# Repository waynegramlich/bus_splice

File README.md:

bus_splice
==========

Splice two buses together.

## Rev A. Issues

* Are terminal blocks oriented backwards?

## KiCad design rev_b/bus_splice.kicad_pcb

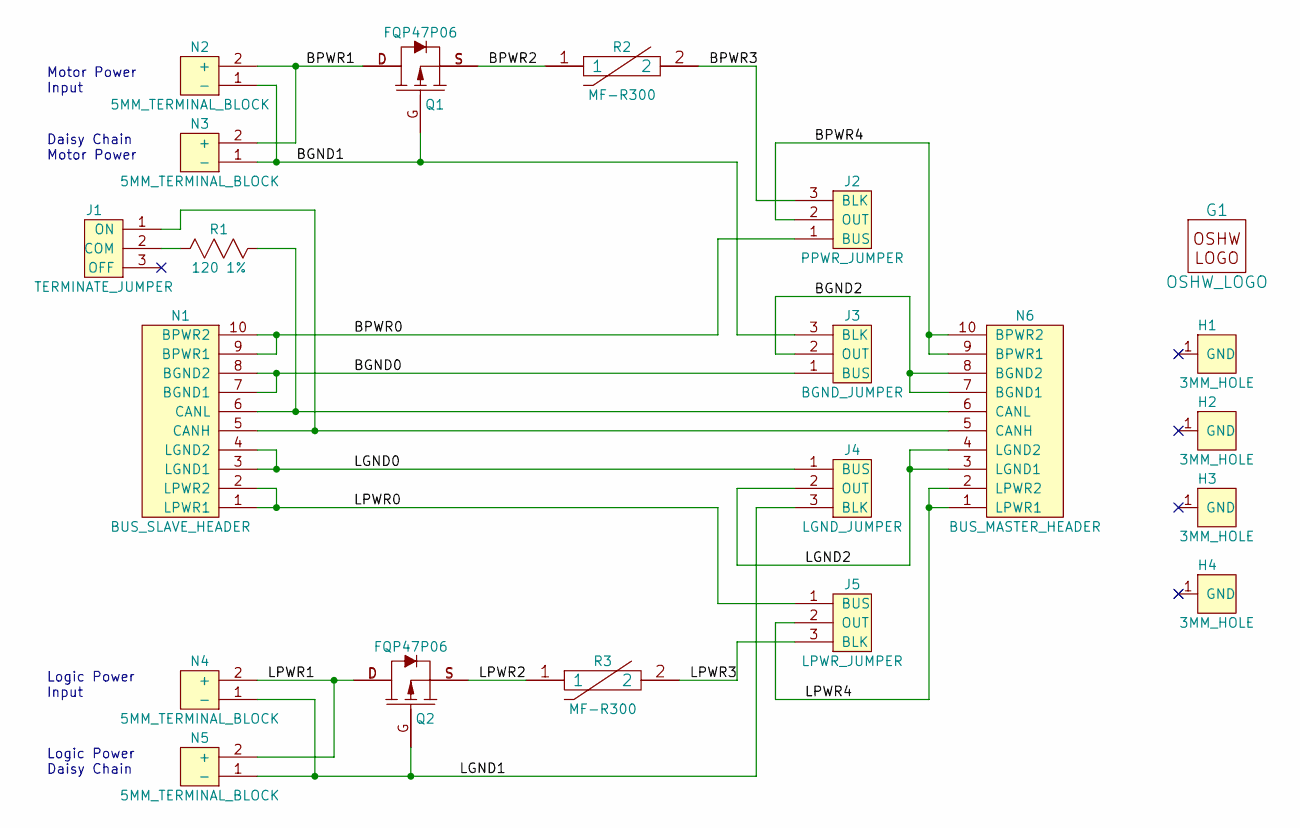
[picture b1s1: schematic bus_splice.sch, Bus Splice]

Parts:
G1: OSHW_LOGO; OSHW_LOGO_400mil
H1, H2, H3, H4: 3MM_HOLE; MountingHole_3mm
J1: TERMINATE_JUMPER; Pin_Header_Straight_1x03
J2: PPWR_JUMPER; Pin_Header_Straight_1x03
J3: BGND_JUMPER; Pin_Header_Straight_1x03
J4: LGND_JUMPER; Pin_Header_Straight_1x03
J5: LPWR_JUMPER; Pin_Header_Straight_1x03
N1: BUS_SLAVE_HEADER; Pin_Header_Straight_2x05_Shrouded
N2, N3, N4, N5: 5MM_TERMINAL_BLOCK; 5MM_TERMINAL_BLOCK_2_POS
N6: BUS_MASTER_HEADER
Q1, Q2: FQP47P06; TO-220_FET-GDS_Horizontal_LargePads
R1: 120 1%; Resistor_Horizontal_400
R2, R3: MF-R300; MF_R300

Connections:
/BGND0: J3.1 (BUS), N1.7 (BGND1), N1.8 (BGND2)
/BGND1: J3.3 (BLK), N2.1 (-), N3.1 (-), Q1.G
/BGND2: J3.2 (OUT), N6.7 (BGND1), N6.8 (BGND2)
/BPWR0: J2.1 (BUS), N1.9 (BPWR1), N1.10 (BPWR2)
/BPWR1: N2.2 (+), N3.2 (+), Q1.D
/BPWR2: Q1.S, R2.1
/BPWR3: J2.3 (BLK), R2.2
/BPWR4: J2.2 (OUT), N6.9 (BPWR1), N6.10 (BPWR2)
/LGND0: J4.1 (BUS), N1.3 (LGND1), N1.4 (LGND2)
/LGND1: J4.3 (BLK), N4.1 (-), N5.1 (-), Q2.G
/LGND2: J4.2 (OUT), N6.3 (LGND1), N6.4 (LGND2)
/LPWR0: J5.1 (BUS), N1.1 (LPWR1), N1.2 (LPWR2)
/LPWR1: N4.2 (+), N5.2 (+), Q2.D
/LPWR2: Q2.S, R3.1
/LPWR3: J5.3 (BLK), R3.2
/LPWR4: J5.2 (OUT), N6.1 (LPWR1), N6.2 (LPWR2)
unnamed: J1.1 (ON), N1.5 (CANH), N6.5 (CANH)
unnamed: J1.2 (COM), R1.1
unnamed: N1.6 (CANL), N6.6 (CANL), R1.2

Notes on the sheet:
Daisy Chain Motor Power
Logic Power Input
Motor Power Input
Logic Power Daisy Chain

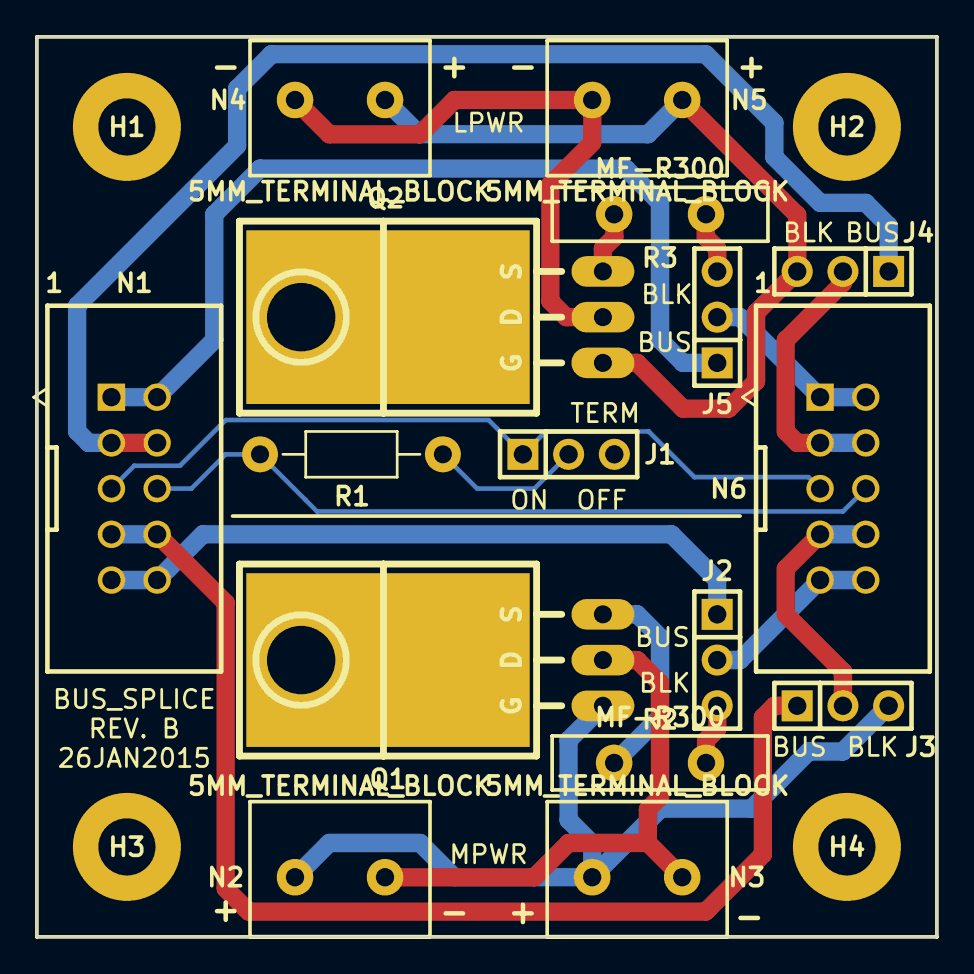
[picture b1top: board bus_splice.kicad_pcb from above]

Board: 2 copper layers, 50.0 x 50.0 mm, 21 parts (1 on the bottom side), 19 nets.

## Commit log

2014-11-03 Got Rev. A
2014-11-16 Wrapped up Rev. A
2015-01-27 Cloned Rev. A.
2015-01-27 Wrapped up Rev. B.

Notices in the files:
rev_b/bus_splice.kicad_pcb:
(C) 20015 GRAMLICH
